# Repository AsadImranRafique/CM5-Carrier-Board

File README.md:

# CM4/CM5 Carrier Board V1

Production build of a compact carrier board for the Raspberry Pi Compute Module 4 and Compute Module 5. The board combines USB-C data and power, Ethernet, 25 W PoE input, M.2 storage and essential peripheral connections in a 120 mm × 40 mm form factor.

## Key Features

- Raspberry Pi Compute Module 4 and Compute Module 5 support
- Two 100-pin Hirose board-to-board connectors
- 120 mm × 40 mm board outline
- Six-layer PCB
- USB-C for data and 5 V at up to 3 A power input
- RJ45 Ethernet MagJack
- 25 W PoE powered-device input
- Jumper-selectable USB-C or PoE power input
- M.2 M-Key connector with support for 2230, 2242 and 2260 modules
- microSD card socket for Compute Module Lite variants
- 3-pin UART JST connector
- 3-pin I²C JST connector
- 3-pin PWM fan JST connector
- PWR and ACT indicator LEDs

## Power Input

The carrier board can be powered through either USB-C or PoE. The active input is selected using the onboard power-selection jumper.

The USB-C input provides 5 V at up to 3 A and uses CC pull-down resistors for source detection. The PoE interface operates as a 25 W powered device through the Ethernet connection.

## Storage

The M.2 M-Key interface supports 2230, 2242 and 2260 module sizes. A microSD card socket is provided for CM4 Lite and CM5 Lite variants without onboard eMMC storage.

## Peripheral Connections

UART, I²C and PWM fan connections are exposed through dedicated 3-pin JST connectors. PWR and ACT LEDs provide visible system-status indication.

## Repository Contents

This repository contains the KiCad design sources for the production V1 board, including:

- Schematic and PCB layout
- Project symbol and footprint libraries
- Component 3D models

## Opening the Project

1. Install [KiCad](https://www.kicad.org/).
2. Clone or download this repository.
3. Open `CM5Carrier.kicad_pro`.

## License

This hardware design is licensed under the [Apache License 2.0](LICENSE).

## Author

Designed by [Asad Imran](https://github.com/AsadImranRafique).

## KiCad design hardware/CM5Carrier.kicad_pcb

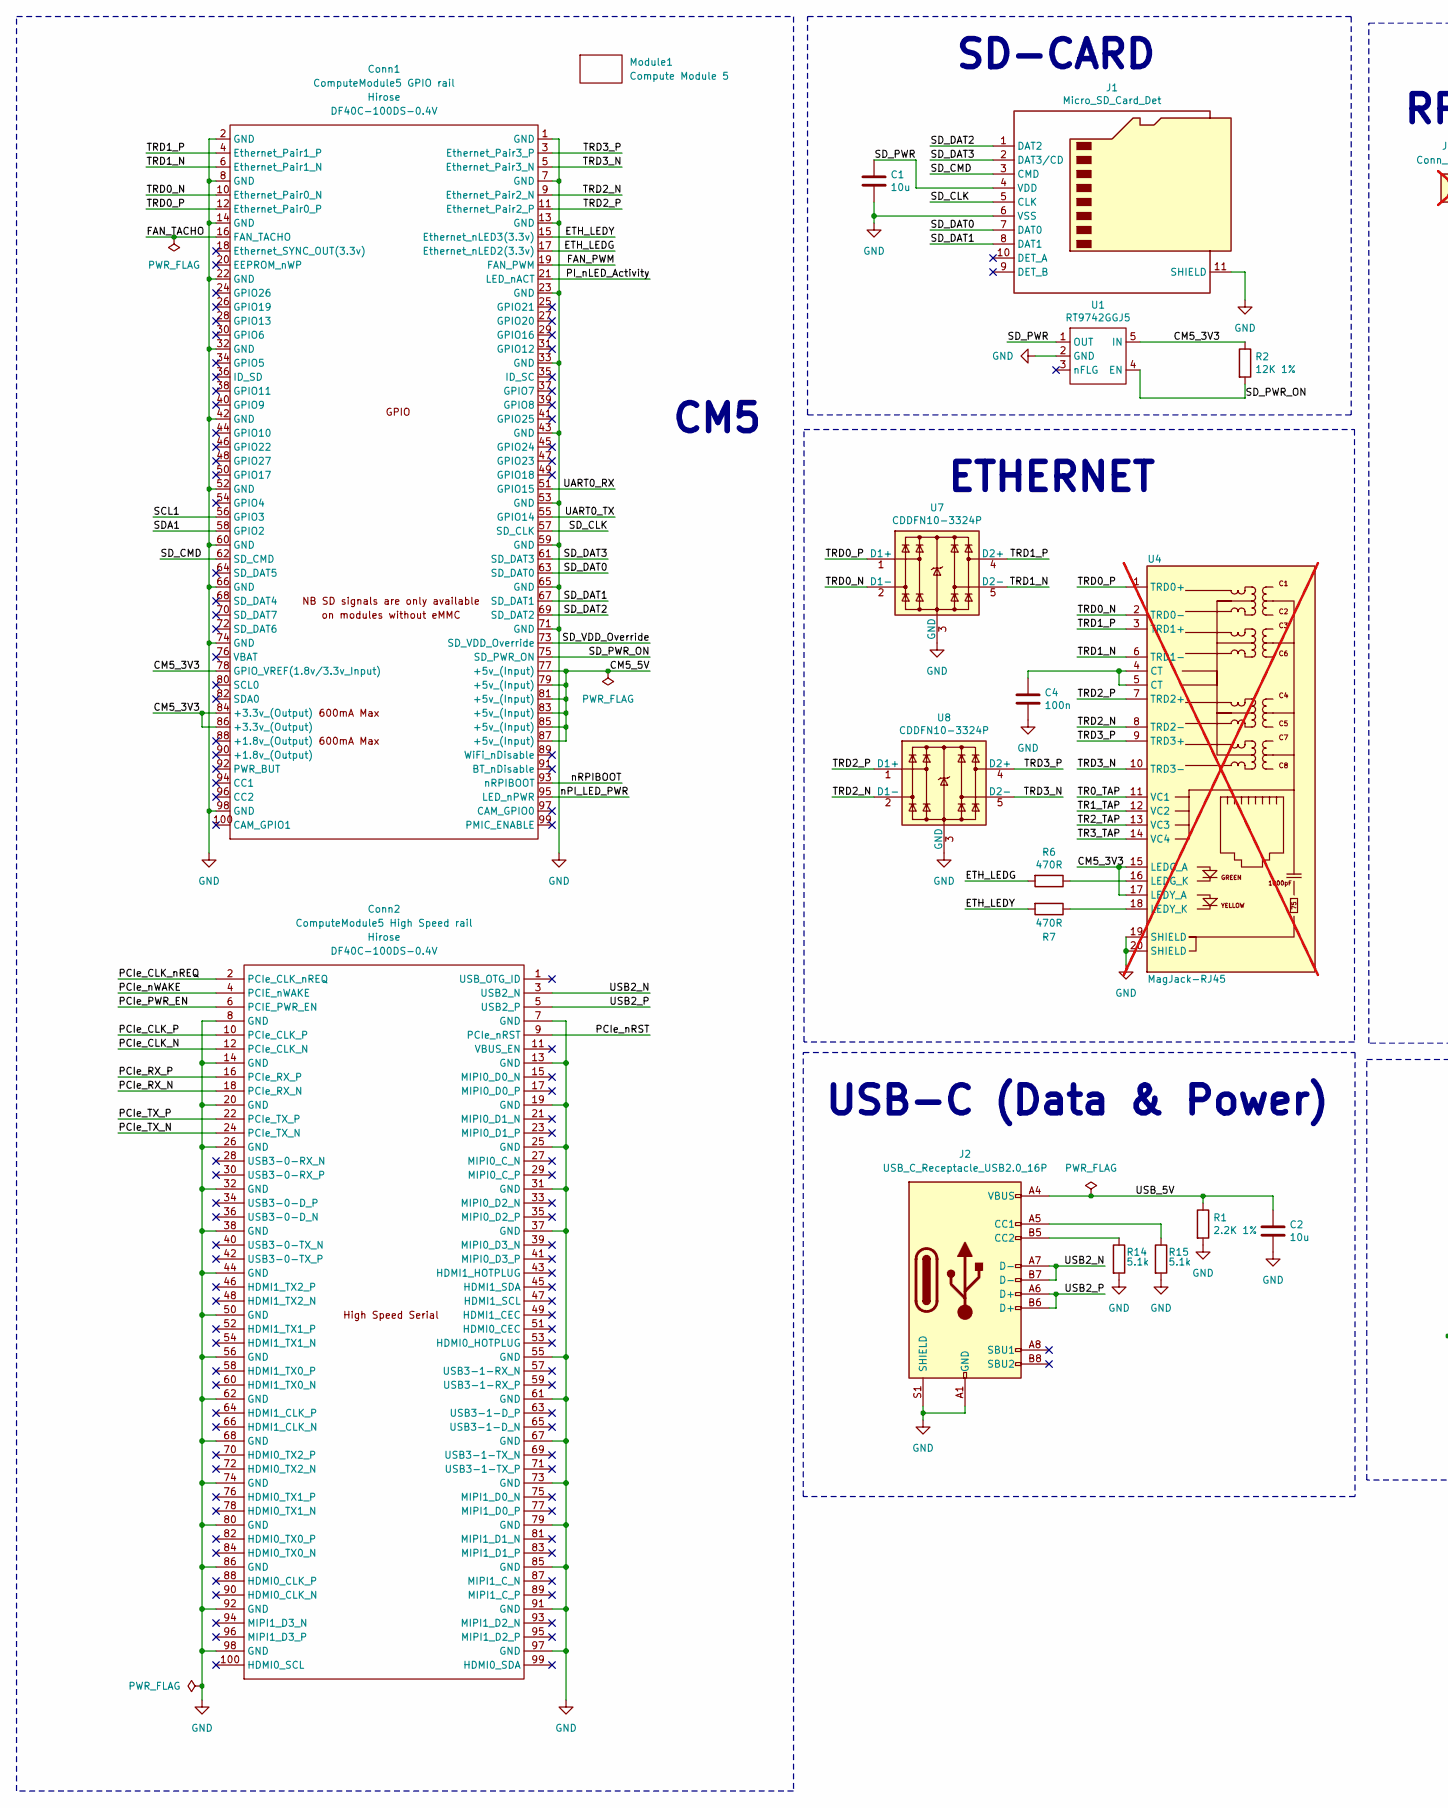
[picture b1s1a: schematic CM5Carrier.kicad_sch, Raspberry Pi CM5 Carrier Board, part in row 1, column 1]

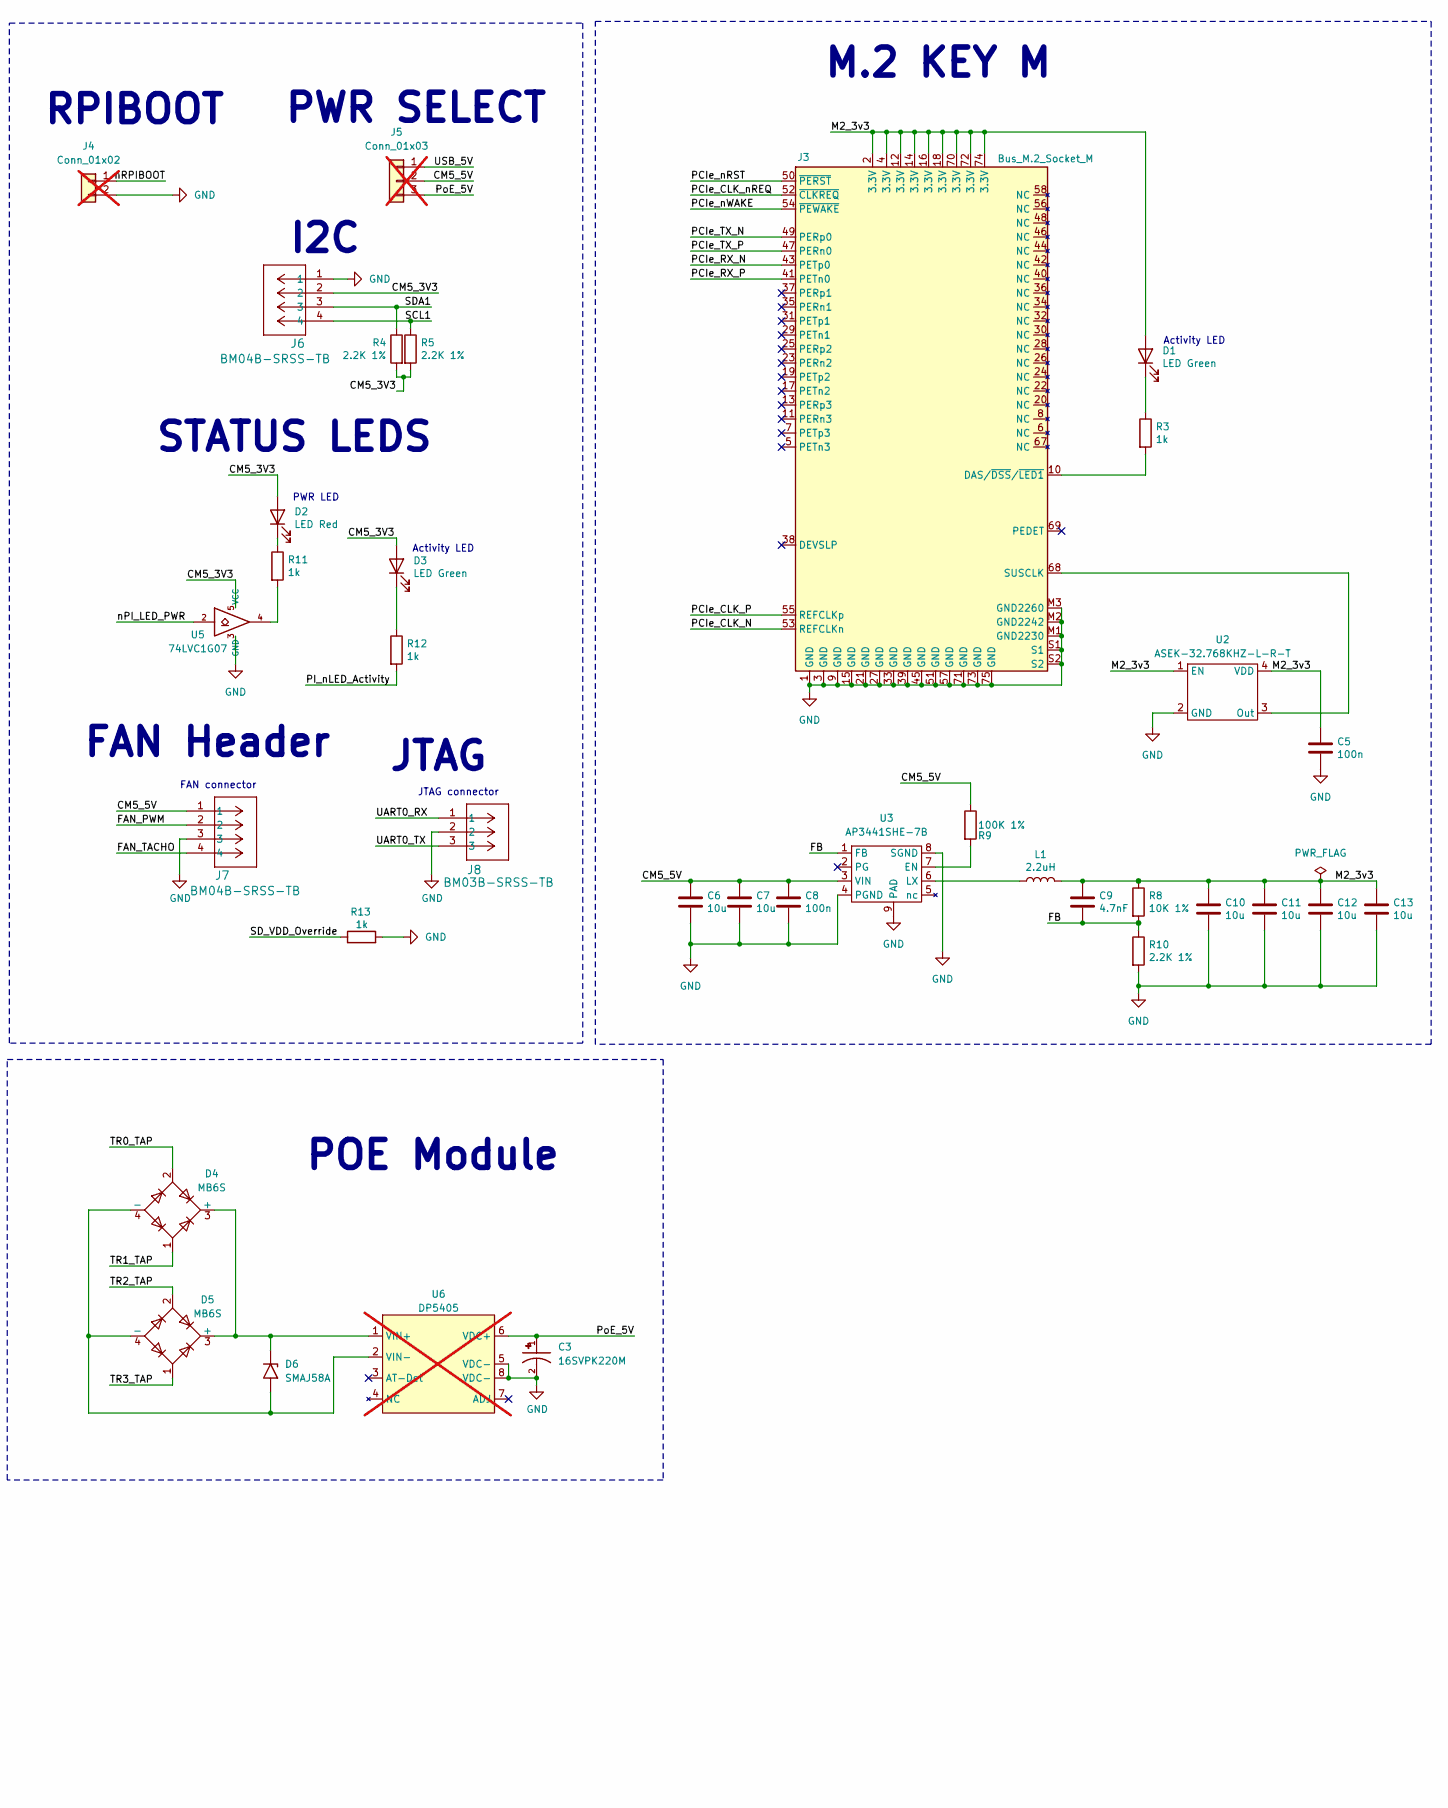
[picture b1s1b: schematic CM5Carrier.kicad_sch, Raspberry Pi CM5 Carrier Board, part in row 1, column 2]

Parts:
C1, C2, C6, C7, C10, C11, C12, C13: 10u; C_0805_2012Metric; Part Number GRM21BR71A106KA73L
C3: 16SVPK220M; CAP_16SVPK220M; Part Number 16SVPK220M
C4, C5, C8: 100n; C_0402_1005Metric; Part Number EMK105B7104KV-F
C9: 4.7nF; C_0402_1005Metric; Part Number CC0402KRX7R9BB472
Conn1: ComputeModule5 GPIO rail; CONN_DF40C-100DS-0.4V51_HIR; Part Number DF40C-100DS-0.4V
Conn2: ComputeModule5 High Speed rail; CONN_DF40C-100DS-0.4V51_HIR; Part Number DF40C-100DS-0.4V
D1, D3: LED Green; LED_0603_1608Metric; Part Number LTST-C190GKT
D2: LED Red; LED_0603_1608Metric; Part Number LTST-C190KRKT
D4, D5: MB6S; TO-269AA; Part Number MB6S
D6: SMAJ58A; D_SMA; Part Number SMAJ58A
J1: Micro_SD_Card_Det; SDCARD_MOLEX_503398-1892; Part Number 5033981892
J2: USB_C_Receptacle_USB2.0_16P; USB4205-GF-A; Part Number USB4205-GF-A
J3: Bus_M.2_Socket_M; M.2 M Key socket; Part Number MDT320M03001
J4: Conn_01x02; PinHeader_1x02_P2.54mm_Vertical; Part Number G800W306018EU; not fitted
J5: Conn_01x03; PinHeader_1x03_P2.54mm_Vertical; Part Number G800W305018EU; not fitted
J6, J7: BM04B-SRSS-TB; JST_SH_BM04B-SRSS-TB_1x04-1MP_P1.00mm_Vertical; Part Number BM04B-SRSS-TB
J8: BM03B-SRSS-TB; JST_SH_BM03B-SRSS-TB_1x03-1MP_P1.00mm_Vertical; Part Number BM03B-SRSS-TB
L1: 2.2uH; L_Bourns_SRP5030CC; Part Number SRP5030CC-2R2M
Module1: Compute Module 5; Raspberry-Pi-5-Compute-Module
R1, R4, R5, R10: 2.2K 1%; R_0402_1005Metric; Part Number RC0402FR-072K2L
R2: 12K 1%; R_0402_1005Metric; Part Number RC0402FR-0712KL
R3, R11, R12, R13: 1k; R_0402_1005Metric; Part Number RC0402FR-071KL
R6, R7: 470R; R_0402_1005Metric; Part Number RC0402FR-07470RL
R8: 10K 1%; R_0402_1005Metric; Part Number RC0402FR-0710KL
R9: 100K 1%; R_0402_1005Metric; Part Number RC0402FR-07100KL
R14, R15: 5.1k; R_0603_1608Metric; Part Number RC0603FR-075K1L
U1: RT9742GGJ5; SOT-23-5; Part Number RT9742GGJ5
U2: ASEK-32.768KHZ-L-R-T; Crystal_SMD_3225-4Pin_3.2x2.5mm; Part Number ASEK-32.768KHZ-L-R-T
U3: AP3441SHE-7B; DFN-8-1EP_2x2mm_P0.5mm_EP1.05x1.75mm; Part Number AP3441SHE-7B
U4: MagJack-RJ45; TRJG0926HENL; Part Number LPJG0926HENL; not fitted
U5: 74LVC1G07; SOT-353_SC-70-5; Part Number 74LVC1G07
U6: DP5405; not fitted
U7, U8: CDDFN10-3324P; USON-10_2.5x1.0mm_P0.5mm; Part Number CDDFN10-3324P

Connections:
/CM5_3V3: Conn1.78 (GPIO_VREF(1.8v/3.3v_Input)), Conn1.84 (+3.3v_(Output)), Conn1.86 (+3.3v_(Output)), D2.2 (A), D3.2 (A), J6.2, R2.1, R4.2, R5.2, U1.5 (IN), U4.15 (LEDG_A), U4.17 (LEDY_A), U5.5 (VCC)
/CM5_5V: C6.1, C7.1, C8.1, Conn1.77 (+5v_(Input)), Conn1.79 (+5v_(Input)), Conn1.81 (+5v_(Input)), Conn1.83 (+5v_(Input)), Conn1.85 (+5v_(Input)), Conn1.87 (+5v_(Input)), J5.2, J7.1, R9.1, U3.3 (VIN)
/ETH_LEDG: Conn1.17 (Ethernet_nLED2(3.3v)), R6.2
/ETH_LEDY: Conn1.15 (Ethernet_nLED3(3.3v)), R7.2
/FAN_PWM: Conn1.19 (FAN_PWM), J7.2
/FAN_TACHO: Conn1.16 (FAN_TACHO), J7.4
/FB: C9.2, R8.2, R10.1, U3.1 (FB)
/M2_3v3: C5.1, C9.1, C10.1, C11.1, C12.1, C13.1, D1.2 (A), J3.2 (3.3V), J3.4 (3.3V), J3.12 (3.3V), J3.14 (3.3V), J3.16 (3.3V), J3.18 (3.3V), J3.70 (3.3V), J3.72 (3.3V), J3.74 (3.3V), L1.2, R8.1, U2.1 (EN), U2.4 (VDD)
/PCIe_CLK_N: Conn2.12 (PCIe_CLK_N), J3.53 (REFCLKn)
/PCIe_CLK_P: Conn2.10 (PCIe_CLK_P), J3.55 (REFCLKp)
/PCIe_CLK_nREQ: Conn2.2 (PCIe_CLK_nREQ), J3.52 (~CLKREQ)
/PCIe_PWR_EN: Conn2.6 (PCIE_PWR_EN)
/PCIe_RX_N: Conn2.18 (PCIe_RX_N), J3.43 (PETp0)
/PCIe_RX_P: Conn2.16 (PCIe_RX_P), J3.41 (PETn0)
/PCIe_TX_N: Conn2.24 (PCIe_TX_N), J3.49 (PERp0)
/PCIe_TX_P: Conn2.22 (PCIe_TX_P), J3.47 (PERn0)
/PCIe_nRST: Conn2.9 (PCIe_nRST), J3.50 (~PERST)
/PCIe_nWAKE: Conn2.4 (PCIE_nWAKE), J3.54 (~PEWAKE)
/PI_nLED_Activity: Conn1.21 (LED_nACT), R12.2
/PoE_5V: C3.1, J5.3, U6.6 (VDC+)
/SCL1: Conn1.56 (GPIO3), J6.4, R5.1
/SDA1: Conn1.58 (GPIO2), J6.3, R4.1
/SD_CLK: Conn1.57 (SD_CLK), J1.5 (CLK)
/SD_CMD: Conn1.62 (SD_CMD), J1.3 (CMD)
/SD_DAT0: Conn1.63 (SD_DAT0), J1.7 (DAT0)
/SD_DAT1: Conn1.67 (SD_DAT1), J1.8 (DAT1)
/SD_DAT2: Conn1.69 (SD_DAT2), J1.1 (DAT2)
/SD_DAT3: Conn1.61 (SD_DAT3), J1.2 (DAT3/CD)
/SD_PWR: C1.1, J1.4 (VDD), U1.1 (OUT)
/SD_PWR_ON: Conn1.75 (SD_PWR_ON), R2.2, U1.4 (EN)
/SD_VDD_Override: Conn1.73 (SD_VDD_Override), R13.1
/TR0_TAP: D4.2, U4.11 (VC1)
/TR1_TAP: D4.1, U4.12 (VC2)
/TR2_TAP: D5.2, U4.13 (VC3)
/TR3_TAP: D5.1, U4.14 (VC4)
/TRD0_N: Conn1.10 (Ethernet_Pair0_N), U4.2 (TRD0-), U7.2 (D1-), U7.9
/TRD0_P: Conn1.12 (Ethernet_Pair0_P), U4.1 (TRD0+), U7.1 (D1+), U7.10
/TRD1_N: Conn1.6 (Ethernet_Pair1_N), U4.6 (TRD1-), U7.5 (D2-), U7.6
/TRD1_P: Conn1.4 (Ethernet_Pair1_P), U4.3 (TRD1+), U7.4 (D2+), U7.7
/TRD2_N: Conn1.9 (Ethernet_Pair2_N), U4.8 (TRD2-), U8.2 (D1-), U8.9
/TRD2_P: Conn1.11 (Ethernet_Pair2_P), U4.7 (TRD2+), U8.1 (D1+), U8.10
/TRD3_N: Conn1.5 (Ethernet_Pair3_N), U4.10 (TRD3-), U8.5 (D2-), U8.6
/TRD3_P: Conn1.3 (Ethernet_Pair3_P), U4.9 (TRD3+), U8.4 (D2+), U8.7
/UART0_RX: Conn1.51 (GPIO15), J8.1
/UART0_TX: Conn1.55 (GPIO14), J8.3
/USB2_N: Conn2.3 (USB2_N), J2.A7 (D-), J2.B7 (D-)
/USB2_P: Conn2.5 (USB2_P), J2.A6 (D+), J2.B6 (D+)
/USB_5V: C2.1, J2.A4 (VBUS), J2.A9 (VBUS), J2.B4 (VBUS), J2.B9 (VBUS), J5.1, R1.1
/nPI_LED_PWR: Conn1.95 (LED_nPWR), U5.2
/nRPIBOOT: Conn1.93 (nRPIBOOT), J4.1
GND: C1.2, C2.2, C3.2, C4.2, C5.2, C6.2, C7.2, C8.2, C10.2, C11.2, C12.2, C13.2, Conn1.1 (GND), Conn1.2 (GND), Conn1.7 (GND), Conn1.8 (GND), Conn1.13 (GND), Conn1.14 (GND), Conn1.22 (GND), Conn1.23 (GND), Conn1.32 (GND), Conn1.33 (GND), Conn1.42 (GND), Conn1.43 (GND), Conn1.52 (GND), Conn1.53 (GND), Conn1.59 (GND), Conn1.60 (GND), Conn1.65 (GND), Conn1.66 (GND), Conn1.71 (GND), Conn1.74 (GND), Conn1.98 (GND), Conn2.7 (GND), Conn2.8 (GND), Conn2.13 (GND), Conn2.14 (GND), Conn2.19 (GND), Conn2.20 (GND), Conn2.25 (GND), Conn2.26 (GND), Conn2.31 (GND), Conn2.32 (GND), Conn2.37 (GND), Conn2.38 (GND), Conn2.44 (GND), Conn2.50 (GND), Conn2.55 (GND), Conn2.56 (GND), Conn2.61 (GND), Conn2.62 (GND), Conn2.67 (GND), Conn2.68 (GND), Conn2.73 (GND), Conn2.74 (GND), Conn2.79 (GND), Conn2.80 (GND), Conn2.85 (GND), Conn2.86 (GND), Conn2.91 (GND), Conn2.92 (GND), Conn2.97 (GND), Conn2.98 (GND), J1.6 (VSS), J1.11 (SHIELD), J2.A1 (GND), J2.A12 (GND), J2.B1 (GND), J2.B12 (GND), J2.S1 (SHIELD), J3.1 (GND), J3.3 (GND), J3.9 (GND), J3.15 (GND), J3.21 (GND), J3.27 (GND), J3.33 (GND), J3.39 (GND), J3.45 (GND), J3.51 (GND), J3.57 (GND), J3.71 (GND), J3.73 (GND), J3.75 (GND), J3.M1 (GND2230), J3.M2 (GND2242), J3.M3 (GND2260), J3.S1, J3.S2, J4.2, J6.1, J7.3, J8.2, R1.2, R10.2, R13.2, R14.2, R15.2, U1.2 (GND), U2.2 (GND), U3.4 (PGND), U3.8 (SGND), U3.9 (PAD), U4.19 (SHIELD), U4.20 (SHIELD), U5.3 (GND), U6.5 (VDC-), U6.8 (VDC-), U7.3 (GND), U7.8 (GND), U8.3 (GND), U8.8 (GND)
unnamed: C4.1, U4.4 (CT), U4.5 (CT)
unnamed: D1.1 (K), R3.1
unnamed: D2.1 (K), R11.1
unnamed: D3.1 (K), R12.1
unnamed: D4.3 (+), D5.3 (+), D6.1 (A1), U6.1 (VIN+)
unnamed: D4.4 (-), D5.4 (-), D6.2 (A2), U6.2 (VIN-)
unnamed: J2.A5 (CC1), R15.1
unnamed: J2.B5 (CC2), R14.1
unnamed: J3.10 (DAS/~DSS/~LED1), R3.2
unnamed: J3.68 (SUSCLK), U2.3 (Out)
unnamed: R11.2, U5.4
unnamed: R9.2, U3.7 (EN)
unnamed: L1.1, U3.6 (LX)
unnamed: R6.1, U4.16 (LEDG_K)
unnamed: R7.1, U4.18 (LEDY_K)

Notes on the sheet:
USB-C (Data & Power)
JTAG connector
I2C
M.2 KEY M
POE Module
PWR SELECT
STATUS LEDS
Activity LED
PWR LED
FAN Header
FAN connector
RPIBOOT
JTAG
ETHERNET
CM5
SD-CARD

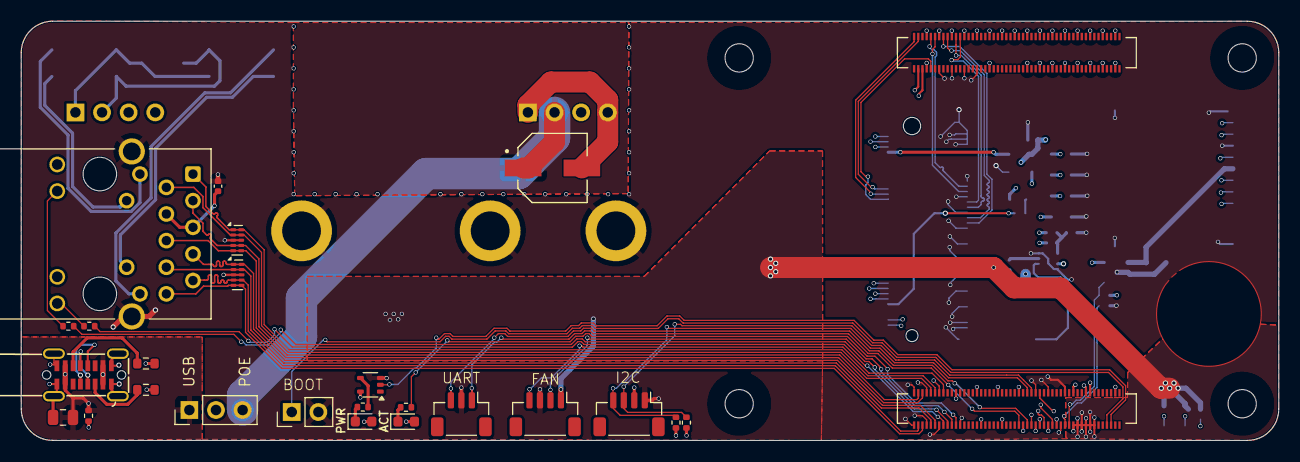
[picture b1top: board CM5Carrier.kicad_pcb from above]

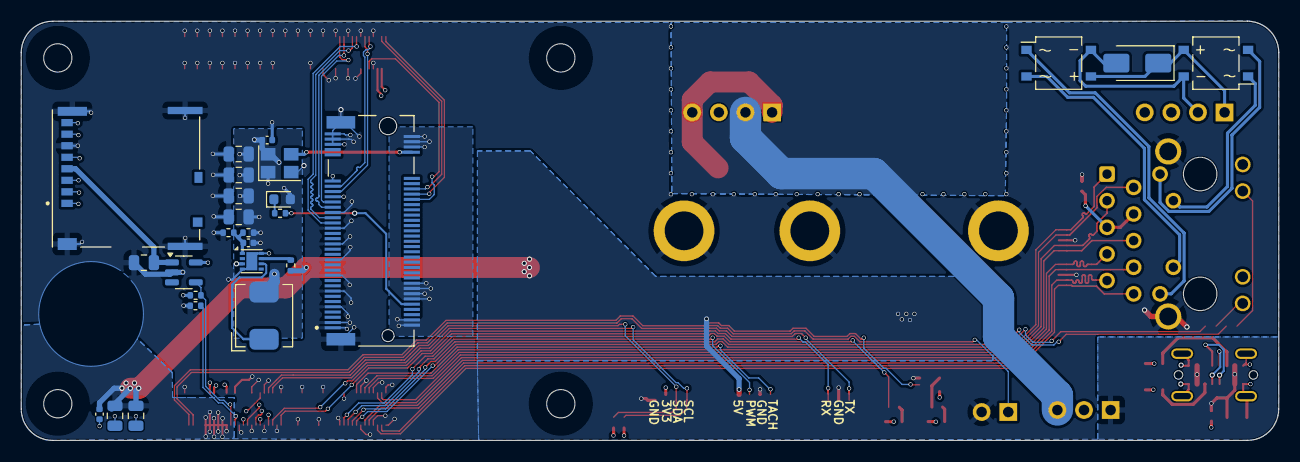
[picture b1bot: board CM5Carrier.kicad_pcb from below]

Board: 6 copper layers, 120.0 x 40.0 mm, 54 parts (26 on the bottom side), 65 nets.

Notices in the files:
parts and their libraries:
Copyright 2016 Accelerated Designs. All rights reserved.
